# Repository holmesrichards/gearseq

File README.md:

# G.E.A.R. Sequencer

This is a voltage controlled trigger sequencer or, perhaps a better term, trigger sequence generator. It can function as a Euclidean rhythm generator, but it can also create other rhythms via different means. It is designed in Kosmo format, though it can presumably be adapted to any other format capable of supplying enough positive voltage for 5 V voltage regulators.

## What it does

Rather than sending triggers in a sequence that is completely specified by the user, the G.E.A.R. Sequencer creates sequences based on user specified parameters.

It offers a choice of four algorithms:

* **G**ap sequence
* **E**uclidean sequence
* **A**DC sequence
* **R**andom sequence

(Hence the name G.E.A.R. Sequencer.) Each algorithm is governed by up to four parameters whose values the user can dial in on potentiometers, or they can be set and dynamically altered using control voltages.

Within limits of program memory and programmer sanity, there is no reason more algorithms could not be added, but these are the four implemented so far.

## Algorithms

**Euclidean sequencing** is familiar and I won't go into the details here — see [http://cgm.cs.mcgill.ca/~godfried/publications/banff-extended.pdf](http://cgm.cs.mcgill.ca/~godfried/publications/banff-extended.pdf) if you need them. The sequence pattern is determined by two parameters: Repetition period (*P*) and number of triggers (*T*). The algorithm distributes the *T* triggers as uniformly as possible among the *P* sequence steps. A third parameter, the offset (*O*), governs not the pattern itself but where the pattern starts/stops relative to where the period starts/stops.

A more novel algorithm is the **gap sequence,** based on the procedure underlying linear scales in tuning theory and the [Three-gap Theorem](https://en.wikipedia.org/wiki/Three-gap_theorem) in mathematics — not that you need to know that. I'm not aware of any prior use of this idea for trigger sequencing although I would be quite surprised if no one else has done it before. In a gap sequence the pattern is defined by three parameters: *P*, *T*, and the generator (*G*). For a given *P* and *T* there is exactly one Euclidean sequence, but there are up to *P*/2 gap sequences corresponding to different generators. Again, the position of the sequence start relative to the period can be specified by *O*. You can find details of the algorithm [here](Docs/gap_sequence.md).

An **ADC sequence** uses a pattern based on digitization of an analog control voltage. You specify *P* and a value to digitize, *V*, as well as, again, *O*. The sequence pattern is the first *P* bits in the digitization of *V*. This is similar to something the Barton Musical Circuits BMC006 Voltage To Rhythm Converter does (though the BMC006 does a lot more with the idea).

A **random sequence** is fairly self explanatory. For a given *P* and *T*, the algorithm distributes *T* triggers randomly within *P* steps. The random pattern is then repeated indefinitely, offset by *O* as with the other types, until a new sequence is requested. Another "parameter" is the throw (*Th*). The value of the throw is not used to determine the pattern, but if it changes, a new random pattern will be chosen.

## Current draw
28 mA +12 V, 0 mA -12 V

## Photos

## Documentation

* [Schematic](Docs/gearseq.pdf)
* PCB layout: [front](Docs/gearseq_layout_front.pdf), [back](Docs/gearseq_layout_back.pdf)
* [BOM](Docs/gearseq_bom.md)
* [Build notes](Docs/build.md)
* [Implementation details](Docs/implementation.md)
* [Gap sequence algorithm](Docs/gap_sequence.md)
* [Usage notes](Docs/usage_notes.md)

## GitHub repository

* [https://github.com/holmesrichards/gearseq](https://github.com/holmesrichards/gearseq)

## Submodules

This repo uses submodules aoKicad and Kosmo_panel, providing libraries needed for KiCad. To clone:

```
git clone git@github.com:holmesrichards/gearseq.git
git submodule init
git submodule update
```

Alternatively do

```
git clone --recurse-submodules git@github.com:holmesrichards/gearseq.git
```

Or if you download the repository as a zip file, you must also click on the "aoKicad" and "Kosmo\_panel" links on the GitHub page (they'll have "@ something" after them) and download them as separate zip files which you can unzip into this repo's aoKicad and Kosmo\_panel directories.

If desired, copy the files from aoKicad and Kosmo\_panel to wherever you prefer (your KiCad user library directory, for instance, if you have one). Then in KiCad, add symbol libraries 

```
aoKicad/ao_symbols
Kosmo_panel/Kosmo
```
and footprint libraries 
```
aoKicad/ao_tht
Kosmo_panel/Kosmo_panel.
```

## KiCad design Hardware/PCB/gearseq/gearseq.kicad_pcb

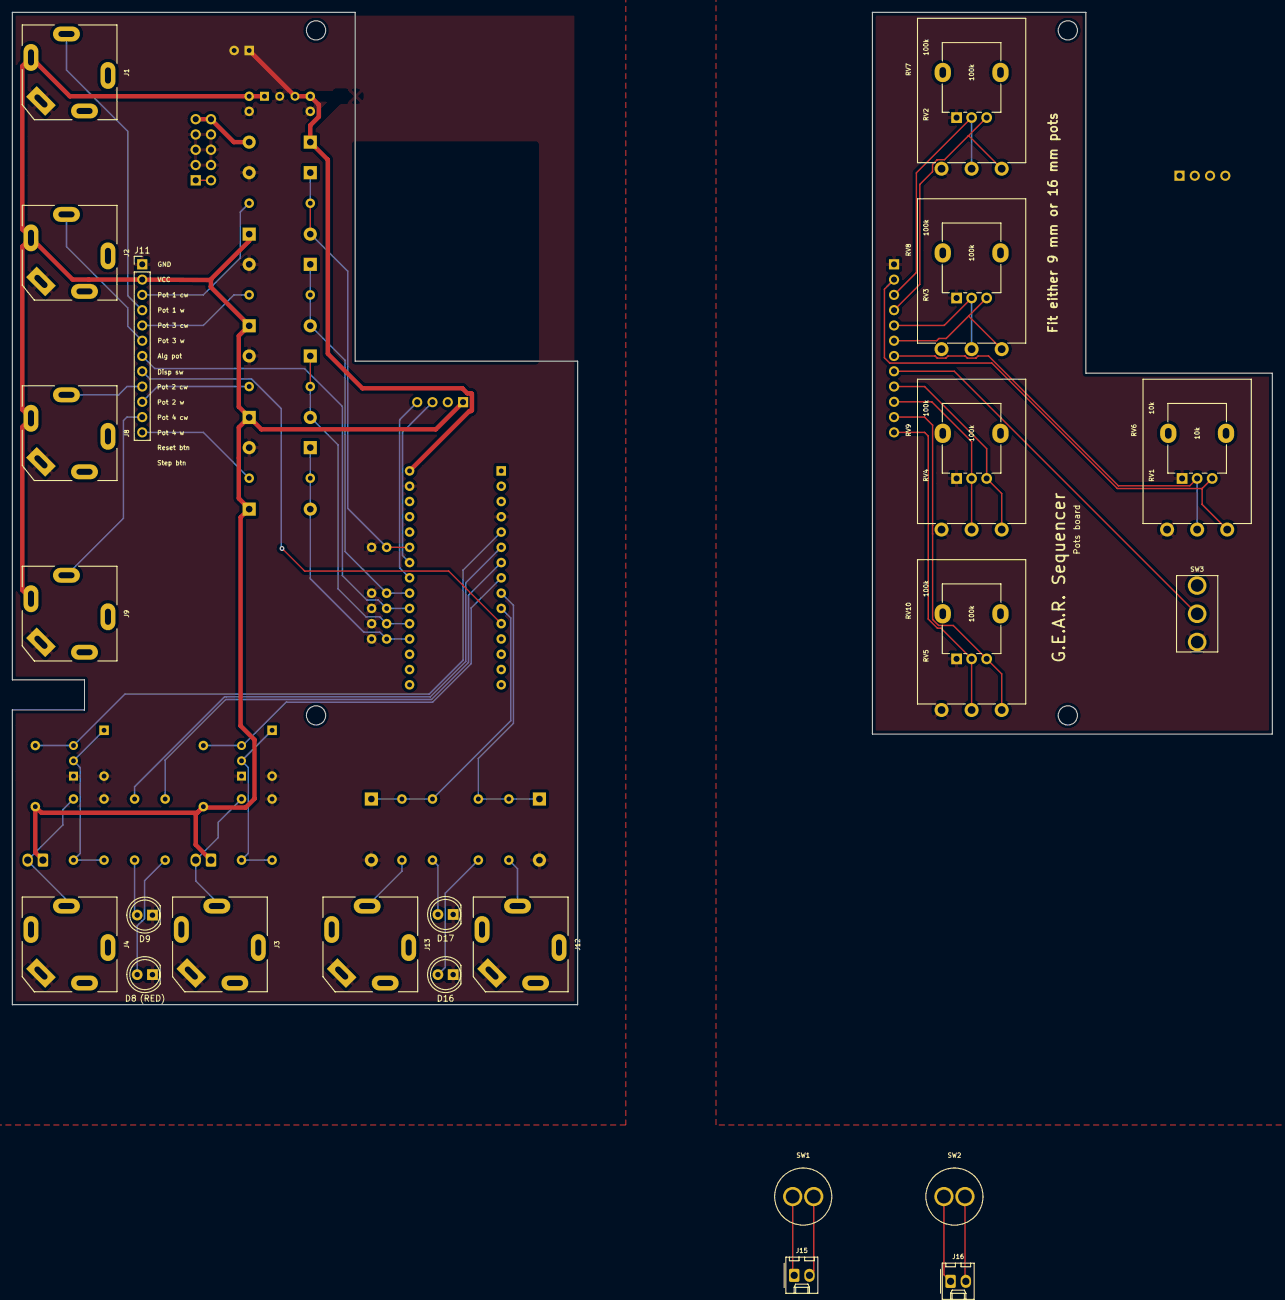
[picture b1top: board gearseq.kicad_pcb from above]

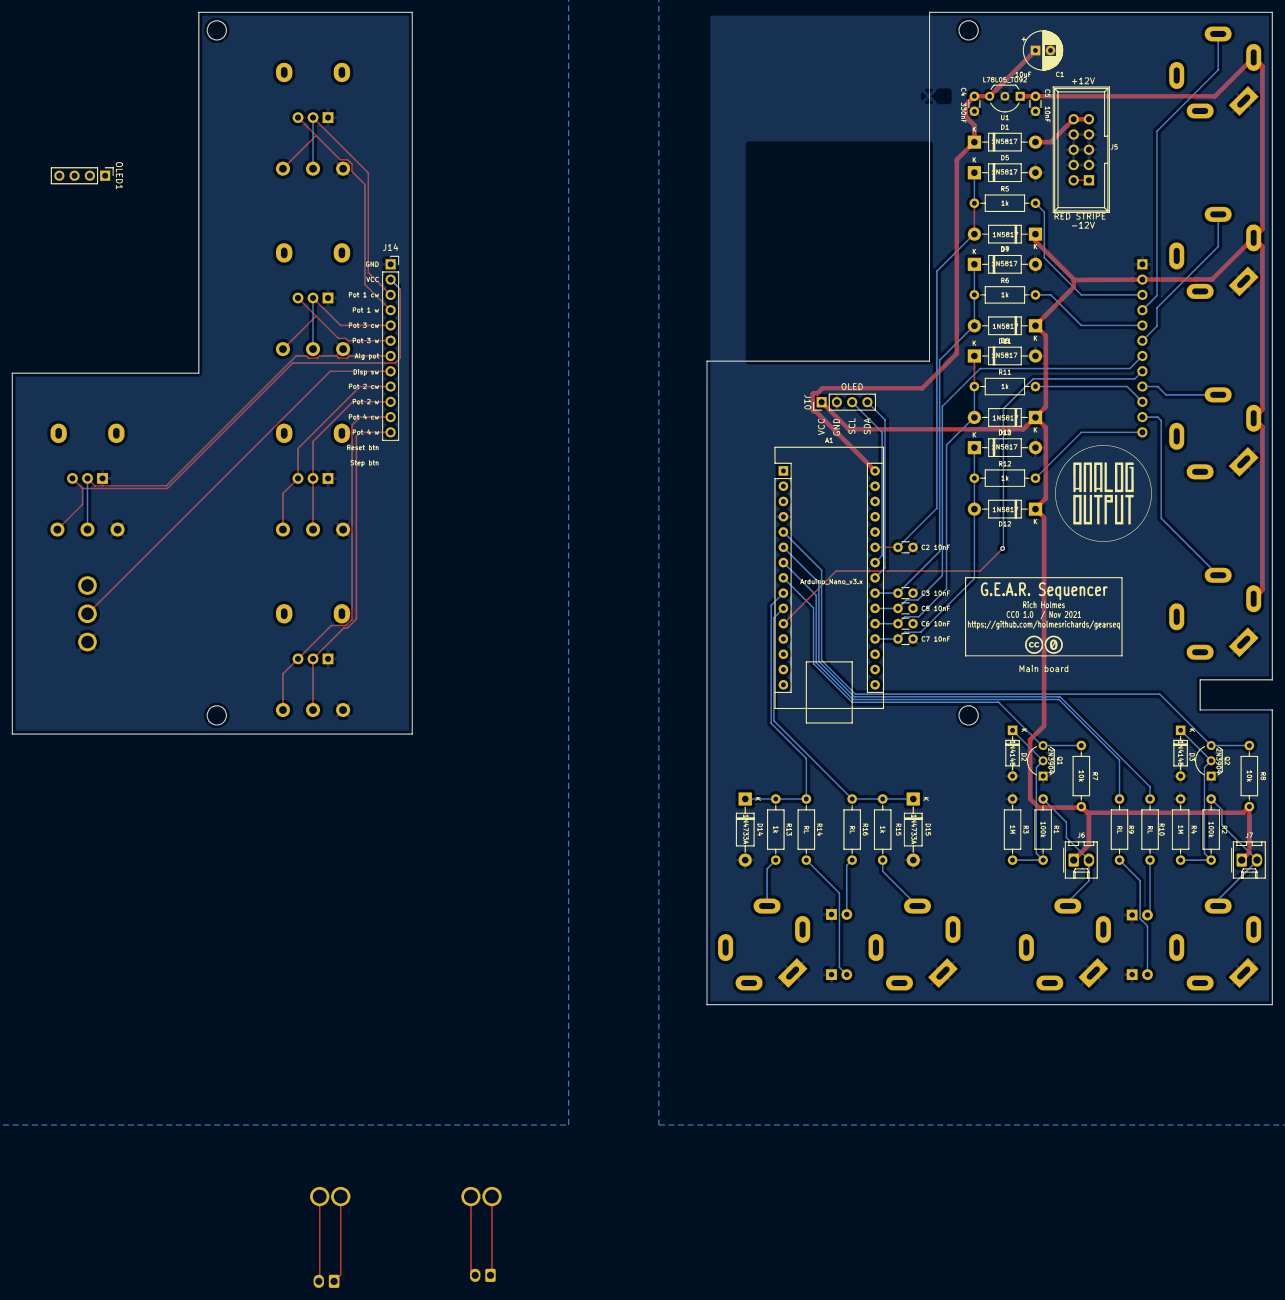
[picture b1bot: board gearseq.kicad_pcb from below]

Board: 2 copper layers, 209.5 x 165.0 mm, 83 parts (49 on the bottom side), 53 nets.

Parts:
A1: Arduino_Nano_v3.x; Arduino_Nano
C1: 10uF; CP_Radial_D6.3mm_P2.50mm
C2, C3, C5, C6, C7, C8: 10nF; C_Disc_D3.0mm_W1.6mm_P2.50mm
C4: 330nF; C_Disc_D3.0mm_W1.6mm_P2.50mm
D1, D4, D5, D6, D7, D10, D11, D12, D13: 1N5817; D_DO-41_SOD81_P10.16mm_Horizontal
D2, D3: 1N4148; D_DO-35_SOD27_P7.62mm_Horizontal
D8: LED_red; LED_D5.0mm
D9, D16, D17: LED_green; LED_D5.0mm
D14, D15: 1N4733A; D_DO-41_SOD81_P10.16mm_Horizontal
GRAF1, GRAF4: Holes; gearseq_panel_holes
GRAF2: AO Logo; analogoutput
GRAF3: CC0 Logo; CC0_logo
H1, H2, H3, H4: MountingHole; MountingHole_3.2mm_M3
J1, J2, J8, J9: AudioJack2_SwitchT; Jack_6.35mm_PJ_629HAN_slots
J3, J4, J12, J13: AudioJack2; Jack_6.35mm_PJ_629HAN_slots
J5: Synth_power_2x5; Power_Header
J6, J7: 2_pin_Molex_header; Molex_KK-254_AE-6410-02A_1x02_P2.54mm_Vertical
J10: Conn_01x04; PinHeader_1x04_P2.54mm_Vertical
J11: Conn_01x12; PinHeader_1x12_P2.54mm_Vertical
J14: Conn_01x12; PinSocket_1x12_P2.54mm_Vertical
J15, J16: 2_pin_Molex_connector; Molex_KK-254_AE-6410-02A_1x02_P2.54mm_Vertical
OLED1: OLED_128X64; PinHeader_1x04_P2.54mm_Vertical
Q1, Q2: 2N3904; TO-92_Inline_Wide
R1, R2: 100k; R_Axial_DIN0207_L6.3mm_D2.5mm_P10.16mm_Horizontal
R3, R4: 1M; R_Axial_DIN0207_L6.3mm_D2.5mm_P10.16mm_Horizontal
R5, R6, R11, R12, R13, R15: 1k; R_Axial_DIN0207_L6.3mm_D2.5mm_P10.16mm_Horizontal
R7, R8: 10k; R_Axial_DIN0207_L6.3mm_D2.5mm_P10.16mm_Horizontal
R9, R10, R14, R16: RL; R_Axial_DIN0207_L6.3mm_D2.5mm_P10.16mm_Horizontal
RV1: 10k; Potentiometer_Alpha_RD901F-40-00D_Single_Vertical_centered
RV2, RV3, RV4, RV5: 100k; Potentiometer_Alpha_RD901F-40-00D_Single_Vertical_centered
RV6: 10k; Potentiometer_Alpha_16mm_Single_Vertical
RV7, RV8, RV9, RV10: 100k; Potentiometer_Alpha_16mm_Single_Vertical
SW1: SW_Push_black; Push_button_A-5050
SW2: SW_Push_red; Push_button_A-5050
SW3: SW_SPST; SPDT-toggle-switch-1M-series
U1: L78L05_TO92; TO-92_Inline_Wide

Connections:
+5V: C5.1, D4.1, D6.1, D10.1, D12.1, J1.TN, J2.TN, J6.1, J7.1, J8.TN, J9.TN, J10.1, J11.2, R7.1, R8.1, U1.1
+5V_1: J14.2, RV1.3, RV6.3
+12V: A1.30, C1.1, C4.1, D1.1, U1.3
/+12_IN: D1.2, J5.9, J5.10
/CLK_IN_J: J4.T, J7.2, R2.2
/PER_J: J13.T, R15.1
/PER_LED: D17.2, R16.1
/RESET_J: J3.T, J6.2, R1.2
/SEQ_J: J12.T, R13.1
/SEQ_LED: D16.2, R14.1
CLOCK_IN: A1.5, Q2.3, R8.2
CLOCK_LED: A1.6, R10.2
CV_1: A1.25, C2.1, D4.2, D5.1, R5.1
CV_2: A1.22, C3.1, D6.2, D7.1, R6.1
CV_3: A1.20, C6.1, D10.2, D11.1, R11.1
CV_4: A1.19, C7.1, D12.2, D13.1, R12.1
DISP_SW: A1.11, J11.8
DISP_SW_P: J14.8, SW3.2
GND: A1.4, A1.29, C1.2, C2.2, C3.2, C4.2, C5.2, C6.2, C7.2, C8.2, D2.2, D3.2, D5.2, D7.2, D8.1, D9.1, D11.2, D13.2, D14.2, D15.2, D16.1, D17.1, J1.S, J2.S, J3.S, J4.S, J5.3, J5.4, J5.5, J5.6, J5.7, J5.8, J8.S, J9.S, J10.2, J11.1, J12.S, J13.S, Q1.1, Q2.1, R3.2, R4.2, U1.2
GND1: J14.1, RV1.1, RV2.1, RV3.1, RV4.1, RV5.1, RV6.1, RV7.1, RV8.1, RV9.1, RV10.1, SW3.1
unnamed: D2.1, Q1.2, R1.1, R3.1
unnamed: D3.1, Q2.2, R2.1, R4.1
unnamed: D8.2, R9.1
unnamed: D9.2, R10.1
unnamed: J5.1, J5.2
unnamed: J15.1, SW1.1
unnamed: J15.2, SW1.2
unnamed: J16.1, SW2.1
unnamed: J16.2, SW2.2
PER_OUT: A1.10, D15.1, R15.2, R16.2
POT_1_CW: J1.T, J11.4
POT_1_CW_P: J14.4, RV2.3, RV7.3
POT_1_W: J11.3, R5.2
POT_1_W_P: J14.3, RV2.2, RV7.2
POT_2_CW: J2.T, J11.6
POT_2_CW_P: J14.6, RV3.3, RV8.3
POT_2_W: J11.5, R6.2
POT_2_W_P: J14.5, RV3.2, RV8.2
POT_3_CW: J8.T, J11.9
POT_3_CW_P: J14.9, RV4.3, RV9.3
POT_3_W: J11.10, R11.2
POT_3_W_P: J14.10, RV4.2, RV9.2
POT_4_CW: J9.T, J11.11
POT_4_CW_P: J14.11, RV5.3, RV10.3
POT_4_W: J11.12, R12.2
POT_4_W_P: J14.12, RV5.2, RV10.2
POT_ALG: A1.21, C8.1, J11.7
POT_ALG_P: J14.7, RV1.2, RV6.2
RESET: A1.8, Q1.3, R7.2
RES_LED: A1.7, R9.2
SCL: A1.24, J10.3
SDA: A1.23, J10.4
SEQ_OUT: A1.9, D14.1, R13.2, R14.2

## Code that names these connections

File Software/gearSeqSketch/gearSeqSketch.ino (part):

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typedef char stateindex;

#define CLOCK_PIN         2
#define CLOCK_LED_PIN     3
#define RESET_LED_PIN     4
#define RESET_IN_PIN      5
#define SEQ_OUT_PIN       6
#define PER_OUT_PIN       7
#define DISP_BLANK_PIN    8

#define ALG_POT  A2
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volatile InputLow<CLOCK_PIN>      i_clock (false);
InputLow<RESET_IN_PIN>            i_reset (false);
Input<DISP_BLANK_PIN>             i_disp_blank (true); // internal pullup on
volatile Output<CLOCK_LED_PIN>    o_clock;
Output<RESET_LED_PIN>             o_reset;
volatile Output<SEQ_OUT_PIN>      o_seq;
volatile Output<PER_OUT_PIN>      o_per;

// current algorithm in use and requested next algorithm
volatile unsigned short int curAlgo = 0;
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  Serial.println("setup ");
#endif
  
  pinMode(CLOCK_LED_PIN, OUTPUT);
  pinMode(RESET_LED_PIN, OUTPUT);
  pinMode(SEQ_OUT_PIN, OUTPUT);
  pinMode(PER_OUT_PIN, OUTPUT);
  pinMode(RESET_IN_PIN, INPUT);
  pinMode(CLOCK_PIN, INPUT);

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
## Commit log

2021-09-29 Initial version
2021-09-29 Fix up sketch, add push buttons
2021-10-03 Panel design
2021-10-31 Add 15 mm pot option; BOM
2021-10-31 Use ao_symbols
2021-11-04 Revise clock and reset inputs, shift board positions
2021-11-04 panel tweak, class-centric sketch
2021-11-06 Fix push button holes; develop and debug software
2021-11-08 Change pot values; README updates; lots of sketch development
2021-11-08 Add capacitors
2021-11-08 Debugging, and display full pending state on change
2021-11-09 Fix (somewhat) reset
2021-11-09 Use DirectIO and move clock handling into interrupt
2021-11-09 Revise README; move gap algorithm description to new document
2021-11-09 Add display blanking switch, stop Period output when None algo, flip OLED
2021-11-11 Display tweak, RL comment
2021-11-12 Final pre fab tweaks, correct oversize LED footprint
2021-11-13 Update docs, generate Gerbers, change PCB hole to notch
2021-11-15 Don't display pending for tiny ADC VALUE changes; handle TRIGS=0 correctly in GAP
2021-11-17 Comment and tweak sketch, edit README
2021-12-03 Documentation updates
2021-12-03 Improve python sketch output; documentation edits
2021-12-04 Images, library updates
2021-12-04 Create LICENSE
2021-12-24 Current draw
2022-01-04 Update git clone links in readme.

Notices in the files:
Software/gearSeqSketch/gearSeqSketch.ino:
Rich Holmes 2021 CC0 1.0
